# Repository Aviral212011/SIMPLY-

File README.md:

# SIMPLY~
SIMPLY is a  compact, custom-designed 8-key macropad with a rotary encoder, built using the Seeed Studio XIAO RP2040.
This project makes the things simple , portable  and customize for productivity and everyday use. this macropad is built in STASIS (organised by hackclub).

---

## Features of our macropad 

*  8 programmable mechanical keys
*  Rotary encoder support (e.g., volume control, scrolling etc)
*  Powered by RP2040 microcontroller
*  Fully customizable firmware 
*  Custom PCB design

---

## Hardware used -

* Microcontroller: Seeed Studio XIAO RP2040
* Switches: 8 ×  Mechanical switches
* Encoder: 1 × Rotary encoder with push button
* PCB: Custom designed (KiCad)

## images 

schematics 

pcb 

pcb 3d view 

case 

top of the case 

bottom of the case 

SIMPLY~

# Onshape link for case -
 https://cad.onshape.com/documents/310f6f8a91e9e86c2858baed/w/dfd8510846a50f933a40a608/e/729a062be51d8e8d5201235f?renderMode=0&uiState=69ef84f2e1636cad1411ec10

---

## 👨‍💻 Author

**Aviral Sen**

---

> SIMPLY~
>
> just made it simple !

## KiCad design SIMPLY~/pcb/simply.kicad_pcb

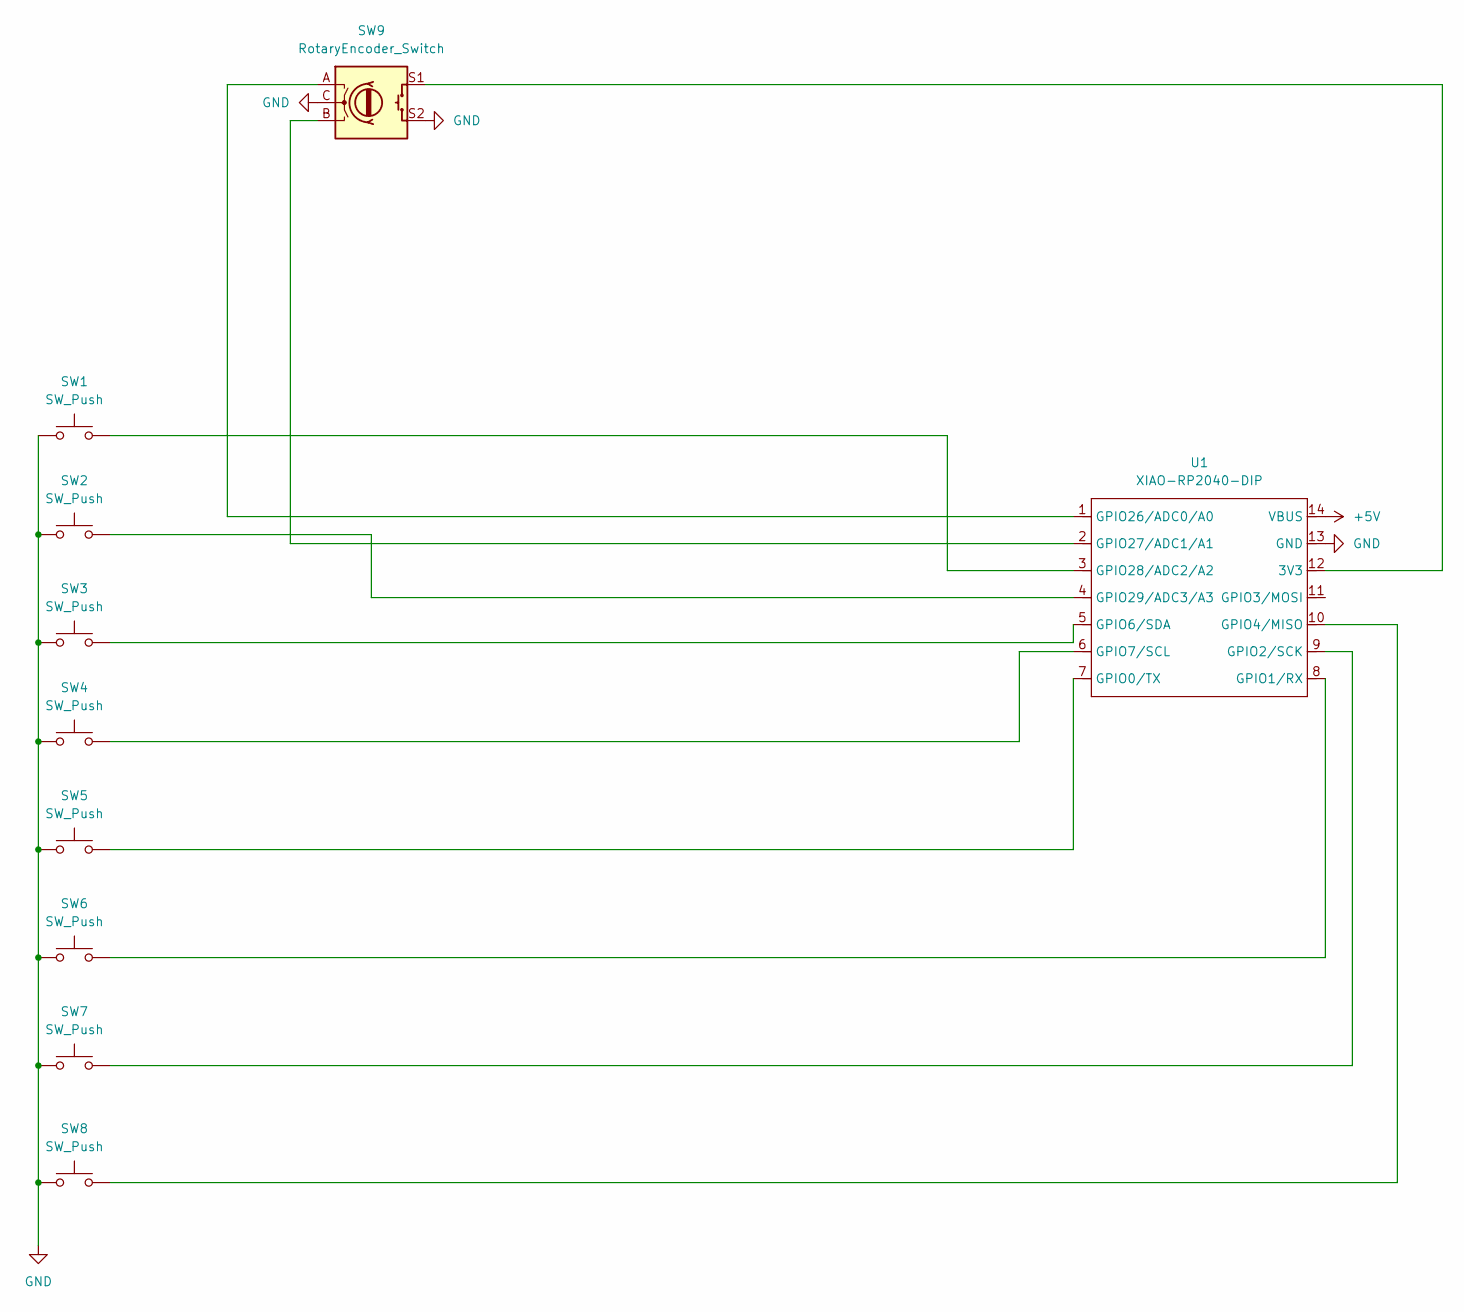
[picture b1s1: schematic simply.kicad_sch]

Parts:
SW1, SW2, SW3, SW4, SW5, SW6, SW7, SW8: SW_Push; SW_Cherry_MX_1.00u_PCB
SW9: RotaryEncoder_Switch; RotaryEncoder_Alps_EC11E-Switch_Vertical_H20mm
U1: XIAO-RP2040-DIP

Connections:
+5V: U1.14 (VBUS)
GND: SW1.1, SW2.1, SW3.1, SW4.1, SW5.1, SW6.1, SW7.1, SW8.1, SW9.C, SW9.S2, U1.13 (GND)
unnamed: SW9.S1, U1.12 (3V3)
unnamed: SW5.2, U1.7 (GPIO0/TX)
unnamed: SW6.2, U1.8 (GPIO1/RX)
unnamed: SW7.2, U1.9 (GPIO2/SCK)
unnamed: SW8.2, U1.10 (GPIO4/MISO)
unnamed: SW3.2, U1.5 (GPIO6/SDA)
unnamed: SW4.2, U1.6 (GPIO7/SCL)
unnamed: SW9.A, U1.1 (GPIO26/ADC0/A0)
unnamed: SW9.B, U1.2 (GPIO27/ADC1/A1)
unnamed: SW1.2, U1.3 (GPIO28/ADC2/A2)
unnamed: SW2.2, U1.4 (GPIO29/ADC3/A3)

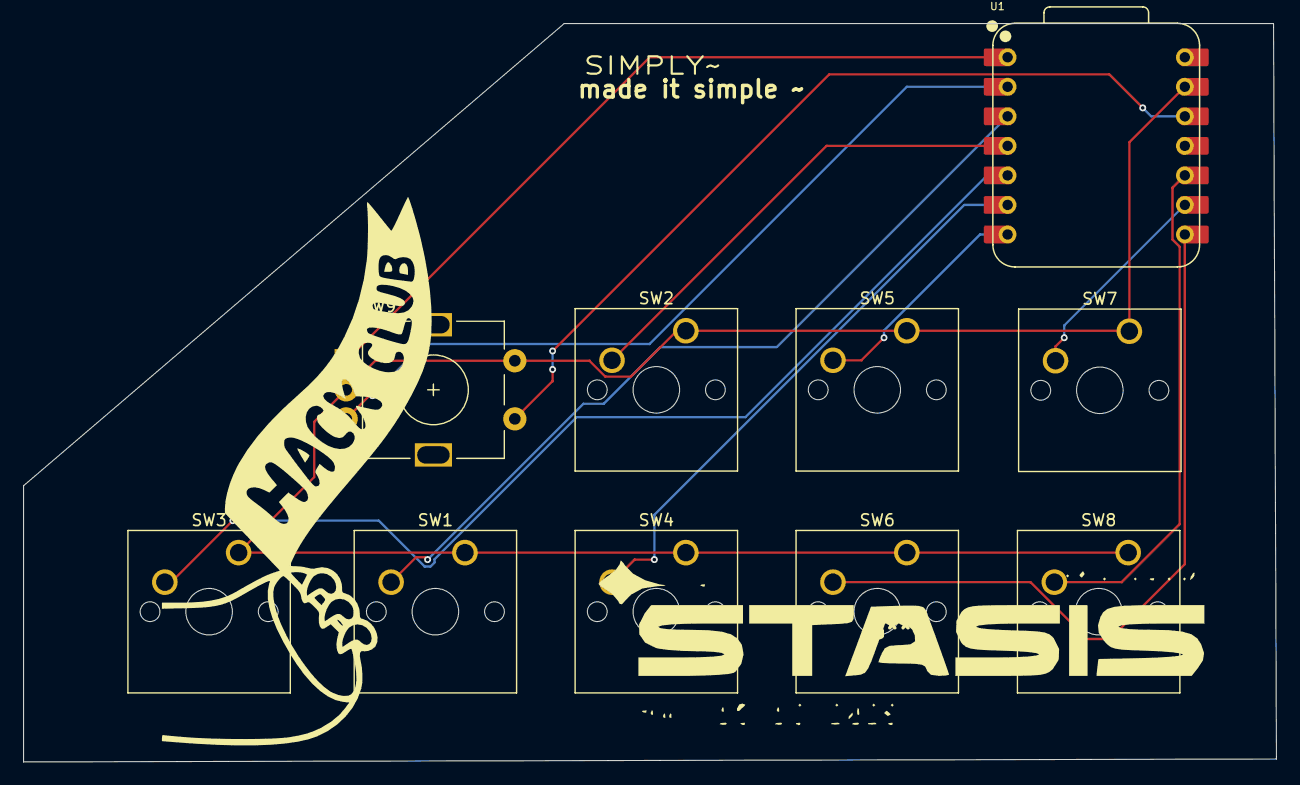
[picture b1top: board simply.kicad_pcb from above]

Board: 2 copper layers, 107.8 x 63.5 mm, 10 parts (0 on the bottom side), 12 nets.
